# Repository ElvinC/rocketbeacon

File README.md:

# rocketbeacon
Configurable sub-GHz radio beacon for amateur rocketry.

**Warning: make sure to comply with your local RF regulations. Some frequency bands require an amateur radio license, others have power or duty cycle limitations.**

## Hardware V1.0
The hardware is designed in KiCad for assembly with JLCPCB. Two versions of the RF front end are available, one optimized for the 220 MHz band and one for the 440 MHz band.

The hardware features:

* STM32WLE5 wireless microcontroller
* Max 22 dBm output power
* CR2032 battery holder
* Can be powered externally by 3.3-5V

## Battery selection and life
**Warning: the beacon doesn't have reverse polarity protection, always double check the battery polarity!** If powered by an external battery (e.g. 1s lipo), connect to the V+ and GND pins. 

CR2032 batteries can't supply much current. When using CR2032 batteries, transmit powers above 16 dBm are not recommended without proper testing. When the voltage drops below 1.8V, the module restarts. An initial delay of a few seconds is thus recommended to allow CR2032 batteries to "recover" after a reset.

To give an idea of the battery life: 3x200 ms beeps at -9, 2, 14 dBm at 4 second intervals achieved 20 hours of battery life with the CR2032. 

Using LiPo batteries, transmit powers up to 22 dBm can be used without issues.

## Assembly V1.1
V1.1 is has some minor tweaks: Larger battery solder pads for improved durability, removal of an unnecessary rx component, and silkscreen tweaks.
The assembled PCB can be ordered by uploading the files from the 1.1 release to JLCPCB. `BOM-beacon-v1.1-220MHz.csv` or `BOM-beacon-v1.1-440MHz.csv` are the BOMs for each frequency version (pick one). Make sure visually that all components (except the 220/440 indicator resistor) are populated.

Some BOM parts may be unavailable at the time of ordering, requiring alternative parts to be selected:

* STM32WLE5CBU6 alternatives: STM32WLE5CCU6 (other in the same family should work too without firmware changes)
* Crystal alternatives: Most 32MHz 10pF 10ppm crystals in the 2016 package should work. E.g. S2132000101080 (though default calibration might be off)
* Capacitor alternatives: Same values in the same package
* Inductors: Same values in the same package

Use the following settings when ordering:

* Layers=2
* Thickness=1.6
* Vias=Tented
* Mark on PCB=Order Number(Specify Position)
* PCBA type=Economic
* Assembly side=Top side
* Tooling holes = Added by Customer

## Assembly V1.0
The assembled PCB can be ordered by uploading the files from `Hardware\beacon\jlcpcb\production_files\V1.0` to JLCPCB. These files are also available in releases as a zip file. `GERBER-beacon.zip` contains the PCB files. For the pick-and-place centroid file, pick either `CPL-beacon-no-pinheader.csv` (cheaper and more compact) or `CPL-beacon-with-pinheader.csv` (assembled with pinheader). `BOM-beacon-v1.0-220MHz.csv` or `BOM-beacon-v1.0-440MHz.csv` are the BOMs for each frequency version (pick one). Make sure visually that all components (except the 220/440 indicator resistor) are populated. If the default STM32WLE5CBU6 is unavailable, the STM32WLE5CCU6 can be selected instead (works with the same firmware).

Use the following settings when ordering:

* Layers=2
* Thickness=1.6
* Vias=Tented
* Mark on PCB=Order Number(Specify Position)
* PCBA type=Economic
* Assembly side=Top side
* Tooling holes = Added by Customer

## Soldering

Other than the assembled PCB, an antenna is required. For a basic quarter wave copper antenna, you can use `length = 0.95 * 0.25 * speed of light / frequency`, where 0.95 is the velocity factor of copper. E.g.

* For 433 MHz, use a 165mm
* For 220 MHz band, Use 324mm

If powered by a button cell battery, solder on a [MY-2032-12](https://www.lcsc.com/product-detail/Battery-Connectors_MYOUNG-MY-2032-12_C964833.html) battery connector. Other similar CR2032 holders work as well, but may require trimming the solder leads to fit the footprint. Melt a little solder on the negative battery terminal before soldering on the battery holder to ensure proper electrical contact.

## Compile and program
The firmware can be modified and compiled with [STM32CubeIDE](https://www.st.com/en/development-tools/stm32cubeide.html).

The main code is located in `Firmware\Core\Src\main.c`. There are three main functions used to generate RF signals:

* `FSKBeep(int8_t powerdBm, uint32_t toneHz, uint32_t lengthMs)`: Synthesize a FSK sequence of alternating 1s and 0s. With a FM receiver, it sounds like a constant audio tone at `toneHz`.
* `CWBeep(int8_t powerdBm, uint32_t lengthMs)`: Generate a continuous wave tone. E.g. for morse code

Note that the `powerdBm` value can range from -9 to 22 dBm. `HAL_Delay(uint32_t millis)` can be used as delay.

Additionally, `play_morse_word(uint8_t* letters, uint8_t len, bool use_cw)` can be used to send an array of letters as morse (either FM or CW).

The default firmware allows for generation of regular FSK or CW tones at various power levels, with options for transmitting callsigns.

Programming the firmware can be done with [STM32CubeProg](https://www.st.com/en/development-tools/stm32cubeprog.html) and a cheap UART to USB dongle (If you don't have one, search "FTDI adaptor" and get one of the red dongles with 6 pins)

* Disconnect power
* Hold down the button
* Set UART adaptor to output 5V power with the jumper, though 3.3V should work as well.
* Connect the UART adaptor to the beacon (make sure Rx->Tx, Tx->Rx, GND->GND and VCC->V+). If unsoldered, hold them at an angle to ensure proper contact as shown below.
* LED should be continuously ON, indicating it has entered bootloader mode.
* In STM32CubeProg, select the UART option and port. Then connect to the MCU.
* In the Erasing & Programming tab, pick the right firmware `Firmware\Debug\rocketbeacon.elf`, and program
* Cycle power to execute the code.

## Reception and tuning
Tune your radio to the programmed frequency. Without calibration, the frequency has a tolerance of roughly +/- 5 KHz in the 70 cm band.

## License and usage
Feel free to use or adapt the hardware design, though if you're a vendor interested in distributing these, please reach out to me at elvin (at) gyroflow.xyz :)

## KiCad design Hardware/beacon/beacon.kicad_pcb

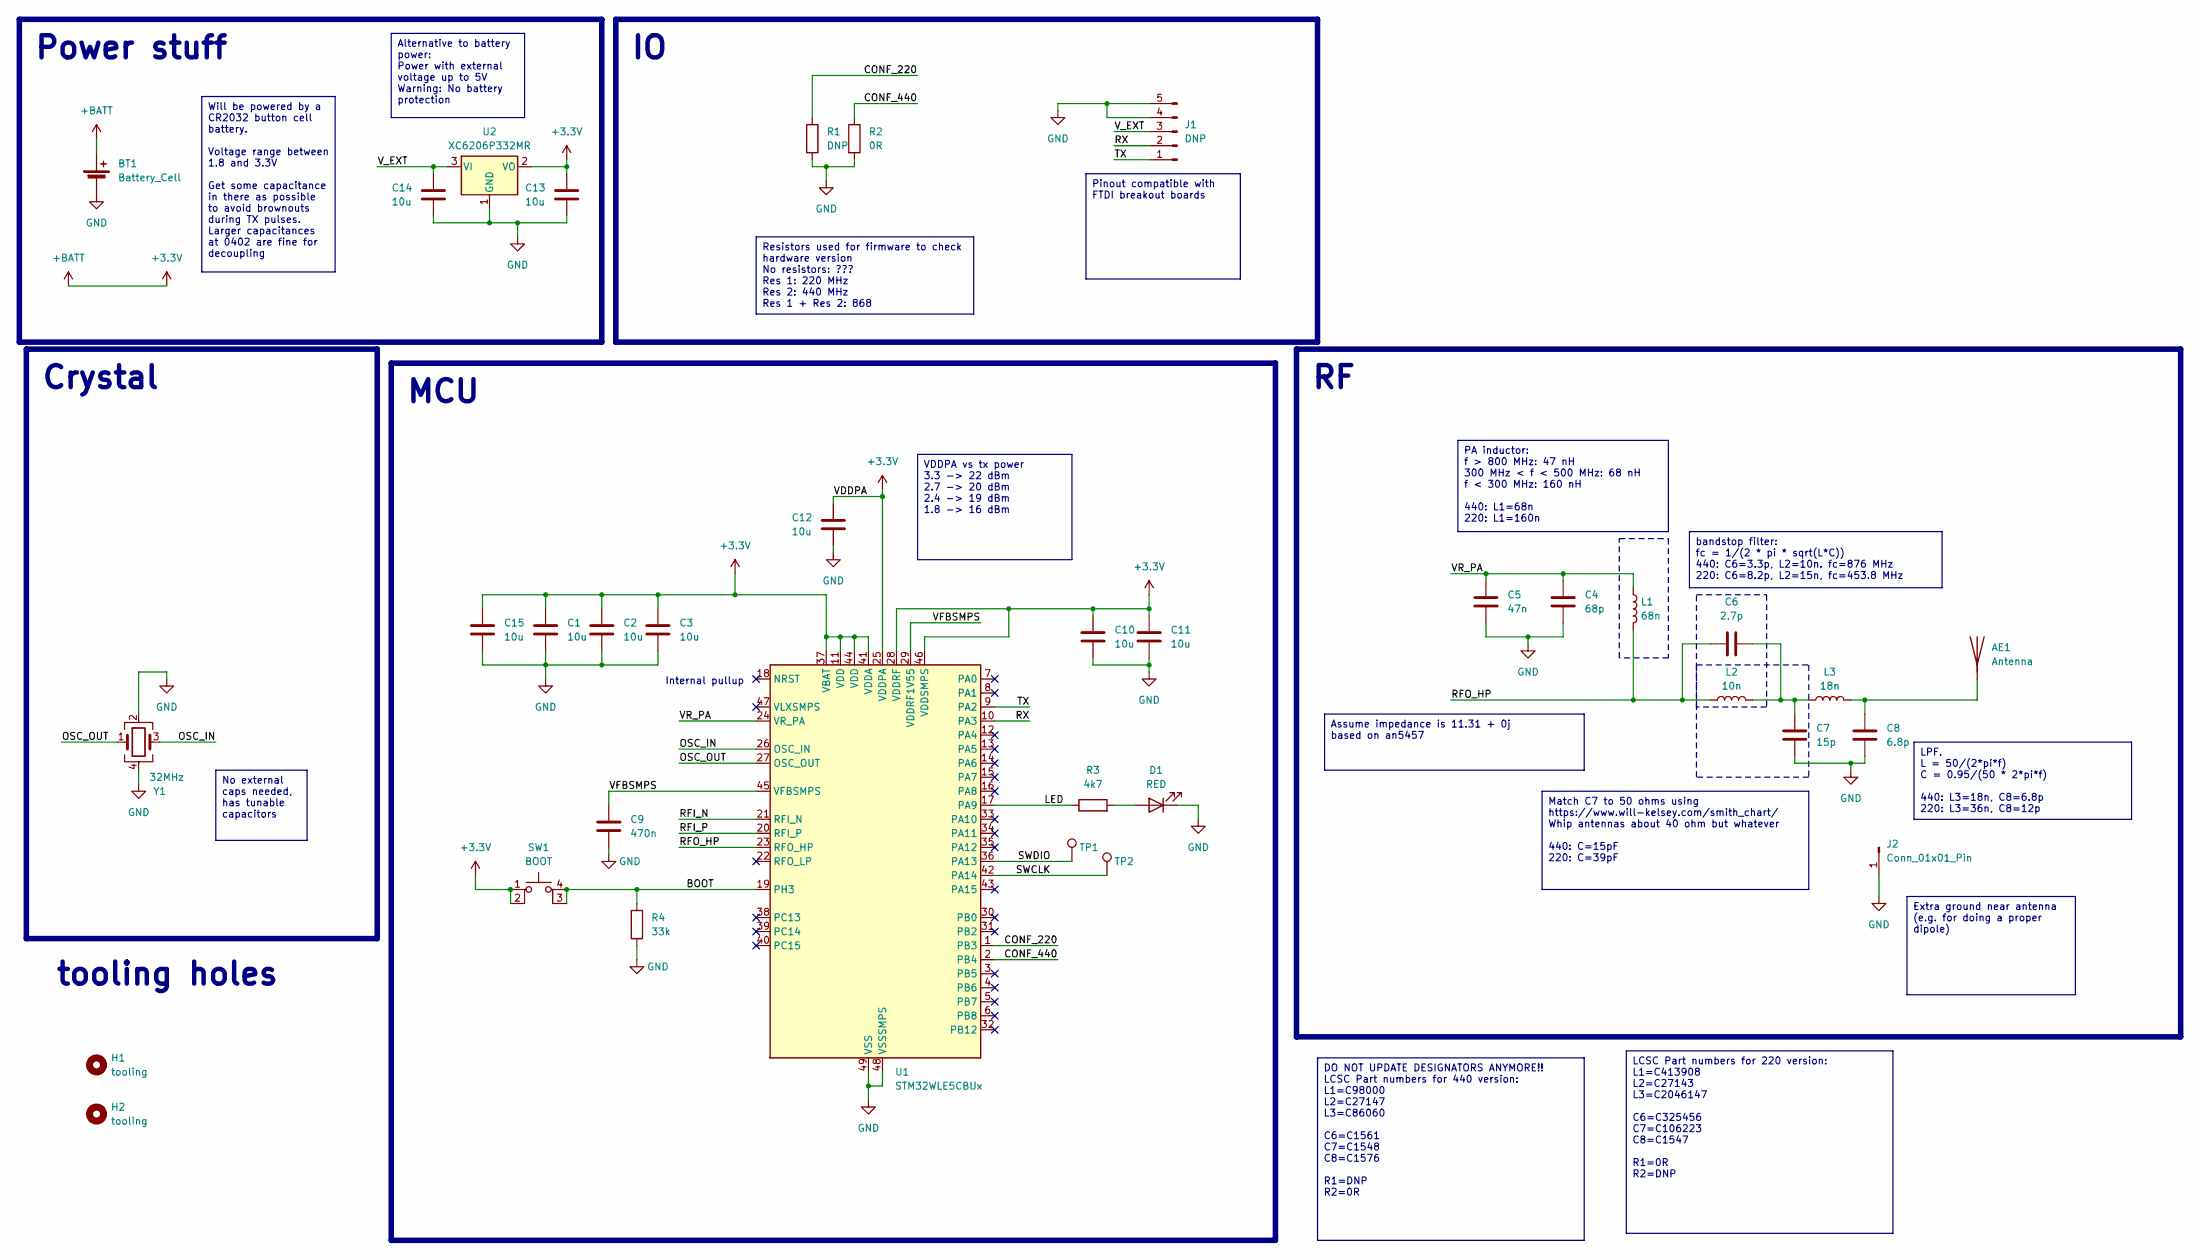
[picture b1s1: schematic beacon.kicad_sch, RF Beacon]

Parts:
AE1: Antenna; whip_antenna
BT1: Battery_Cell; MY-2032-12
C1, C2, C3, C10, C11, C12, C13, C14, C15: 10u; C_0402_1005Metric
C4: 68p; C_0402_1005Metric
C5: 47n; C_0402_1005Metric
C6: 2.7p; C_0402_1005Metric
C7: 15p; C_0402_1005Metric
C8: 6.8p; C_0402_1005Metric
C9: 470n; C_0402_1005Metric
D1: RED; LED_0603_1608Metric
H1, H2: tooling; toolinghole
J1: DNP; PinHeader_1x05_P2.54mm_Horizontal
J2: Conn_01x01_Pin; small_pad
L1: 68n; L_0402_1005Metric
L2: 10n; L_0402_1005Metric
L3: 18n; L_0402_1005Metric
R1: DNP; R_0402_1005Metric
R2: 0R; R_0402_1005Metric
R3: 4k7; R_0402_1005Metric
R4: 33k; R_0402_1005Metric
SW1: BOOT; SW_1TS026A
TP1, TP2: TestPoint_Pad_D1.0mm
U1: STM32WLE5CBUx; QFN-48-1EP_7x7mm_P0.5mm_EP5.6x5.6mm
U2: XC6206P332MR; SOT-23
Y1: 32MHz; Crystal_SMD_2016-4Pin_2.0x1.6mm; LCSC C383840

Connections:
+3.3V: BT1.1 (+), C1.1, C2.1, C3.1, C10.1, C11.1, C12.1, C13.1, C15.1, SW1.1, SW1.2, U1.11 (VDD), U1.25 (VDDPA), U1.28 (VDDRF), U1.37 (VBAT), U1.41 (VDDA), U1.44 (VDD), U1.46 (VDDSMPS), U2.2 (VO)
/BOOT: R4.2, SW1.3 (K), SW1.4 (A), U1.19 (PH3)
/CONF_220: R1.1, U1.1 (PB3)
/CONF_440: R2.1, U1.2 (PB4)
/LED: R3.1, U1.17 (PA9)
/OSC_IN: U1.26 (OSC_IN), Y1.3
/OSC_OUT: U1.27 (OSC_OUT), Y1.1
/RFI_N: U1.21 (RFI_N)
/RFI_P: U1.20 (RFI_P)
/RFO_HP: C6.1, L1.2, L2.1, U1.23 (RFO_HP)
/RX: J1.2, U1.10 (PA3)
/SWCLK: TP2.1, U1.42 (PA14)
/SWDIO: TP1.1, U1.36 (PA13)
/TX: J1.1, U1.9 (PA2)
/VFBSMPS: C9.1, U1.29 (VDDRF1V55), U1.45 (VFBSMPS)
/VR_PA: C4.1, C5.1, L1.1, U1.24 (VR_PA)
/V_EXT: C14.1, J1.3, U2.3 (VI)
GND: BT1.2 (-), C1.2, C2.2, C3.2, C4.2, C5.2, C7.2, C8.2, C9.2, C10.2, C11.2, C12.2, C13.2, C14.2, C15.2, D1.1 (K), J1.4, J1.5, J2.1, R1.2, R2.2, R4.1, U1.48 (VSSSMPS), U1.49 (VSS), U2.1 (GND), Y1.2, Y1.4
unnamed: AE1.1 (A), C8.1, L3.2
unnamed: C6.2, C7.1, L2.2, L3.1
unnamed: D1.2 (A), R3.2

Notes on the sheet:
No external caps needed, has tunable capacitors
Match C7 to 50 ohms using https://www.will-kelsey.com/smith_chart/ Whip antennas about 40 ohm but whatever 440: C=15pF 220: C=39pF
Resistors used for firmware to check hardware version No resistors: ??? Res 1: 220 MHz Res 2: 440 MHz Res 1 + Res 2: 868
PA inductor: f > 800 MHz: 47 nH 300 MHz < f < 500 MHz: 68 nH f < 300 MHz: 160 nH 440: L1=68n 220: L1=160n
Extra ground near antenna (e.g. for doing a proper dipole)
bandstop filter: fc = 1/(2 * pi * sqrt(L*C)) 440: C6=3.3p, L2=10n. fc=876 MHz 220: C6=8.2p, L2=15n, fc=453.8 MHz
VDDPA vs tx power 3.3 -> 22 dBm 2.7 -> 20 dBm 2.4 -> 19 dBm 1.8 -> 16 dBm
LCSC Part numbers for 220 version: L1=C413908 L2=C27143 L3=C2046147 C6=C325456 C7=C106223 C8=C1547 R1=0R R2=DNP
Will be powered by a CR2032 button cell battery. Voltage range between 1.8 and 3.3V Get some capacitance in there as possible to avoid brownouts during TX pulses. Larger capacitances at 0402 are fine for decoupling
Assume impedance is 11.31 + 0j based on an5457
LPF. L = 50/(2*pi*f) C = 0.95/(50 * 2*pi*f) 440: L3=18n, C8=6.8p 220: L3=36n, C8=12p
Pinout compatible with FTDI breakout boards
Alternative to battery power: Power with external voltage up to 5V Warning: No battery protection
DO NOT UPDATE DESIGNATORS ANYMORE!! LCSC Part numbers for 440 version: L1=C98000 L2=C27147 L3=C86060 C6=C1561 C7=C1548 C8=C1576 R1=DNP R2=0R
tooling holes
Power stuff
MCU
Crystal
Internal pullup

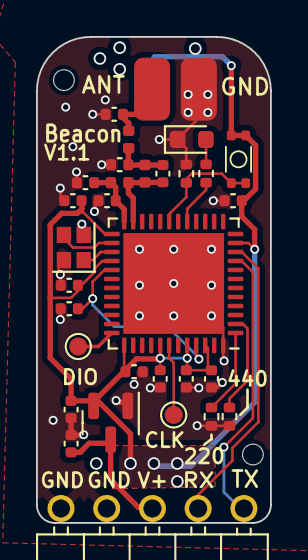
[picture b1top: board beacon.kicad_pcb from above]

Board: 2 copper layers, 13.0 x 27.0 mm, 35 parts (1 on the bottom side), 19 nets.

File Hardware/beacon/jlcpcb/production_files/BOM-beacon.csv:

Comment,Designator,Footprint,LCSC
STM32WLE5CBUx,U1,QFN-48-1EP_7x7mm_P0.5mm_EP5.6x5.6mm,C1121847
68p,C4,C_0402_1005Metric,C14441
15p,C7,C_0402_1005Metric,C1548
10u,"C1,C10,C11,C12,C13,C14,C15,C2,C3",C_0402_1005Metric,C15525
2.7p,C6,C_0402_1005Metric,C1561
6.8p,C8,C_0402_1005Metric,C1576
RED,D1,LED_0603_1608Metric,C2286
33k,R4,R_0402_1005Metric,C25779
4k7,R3,R_0402_1005Metric,C25900
15n,L4,L_0402_1005Metric,C27143
10n,L2,L_0402_1005Metric,C27147
47n,C5,C_0402_1005Metric,C272875
32MHz,Y1,Crystal_SMD_2016-4Pin_2.0x1.6mm,C383840
470n,C9,C_0402_1005Metric,C47339
XC6206P332MR,U2,SOT-23,C5446
18n,L3,L_0402_1005Metric,C86060
BOOT,SW1,SW_1TS026A,C913778
68n,L1,L_0402_1005Metric,C98000
DNP,J1,PinHeader_1x05_P2.54mm_Horizontal,
~,TP2,TestPoint_Pad_D1.0mm,
DNP,R1,R_0402_1005Metric,
~,TP1,TestPoint_Pad_D1.0mm,
0R,R2,R_0402_1005Metric,
Antenna,AE1,whip_antenna,
Battery_Cell,BT1,MY-2032-12,
Conn_01x01_Pin,J2,small_pad,
tooling,H2,toolinghole,
tooling,H1,toolinghole,

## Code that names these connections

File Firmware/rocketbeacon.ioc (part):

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Mcu.Name=STM32WLE5CBUx
Mcu.Package=UFQFPN48
Mcu.UserName=STM32WLE5CBUx
PA13.Mode=Serial_Wire
PA13.Signal=DEBUG_JTMS-SWDIO
PA14.Mode=Serial_Wire
PA14.Signal=DEBUG_JTCK-SWCLK
PA2.Mode=Asynchronous
PA2.Signal=USART2_TX
PA3.Mode=Asynchronous
PA3.Signal=USART2_RX
PA9.GPIOParameters=GPIO_Label
PA9.GPIO_Label=LED
PA9.Signal=GPIO_Output
PB3.GPIOParameters=GPIO_Label
PB3.GPIO_Label=CONF_440
PB3.Signal=GPIO_Input
PB4.GPIOParameters=GPIO_Label
PB4.GPIO_Label=CONF_868
PB4.Signal=GPIO_Input
PH3-BOOT0.GPIOParameters=GPIO_Label
PH3-BOOT0.GPIO_Label=BOOT
PH3-BOOT0.Signal=GPIO_Input
RCC.HSEPRES=2
RCC.HSE_VALUE=32000000
RCC.SYSCLKFreq_VALUE=16000000
RCC.SYSCLKSource=RCC_SYSCLKSOURCE_HSE
board=custom

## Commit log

2023-07-24 Initial version
2023-08-08 Files for version 1
2023-08-08 Add assembly files and edit readme
2023-08-17 Clean code a bit
2023-08-25 add csv files
2023-09-13 Added easy config lines
    Go to lines 345-382 to be able to easily configure the beacons to do various combinations of CW, FSK, and morse code beeps
2023-09-16 Edit readme
2023-09-16 Add compilation files to gitignore
2023-09-16 Add max power setting
2023-09-16 Add battery info to readme
2023-09-16 Decrease default tx power for coin cell batteries
2023-10-27 Add centroid file without pinheader
2023-11-28 Add note about alternative MCU option
2024-01-09 Audio testing
2024-02-01 Add rx test
2024-04-17 Revert rx test
2025-03-28 V1.1 beacon files
2025-03-28 v1.1 step file and tweaked readme
2026-01-29 chore: update readme and instructions to reflect current jlcpcb options
